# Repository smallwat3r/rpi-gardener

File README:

RPI DHT22 SERVER
----------------

This project contains necessarry files and scripts to read temperature and 
humidity data from a DHT22 sensor, wired to a Raspberry Pi 4. It stores the 
results every 2 seconds in a local Sqlite database, and renders them on a bare 
simple frontend using ChartJS powered by Flask and web-sockets.

REQUIREMENTS
------------

Get and build Python 3.12 from source

    sudo apt update
    sudo apt install build-essential zlib1g-dev libncurses5-dev libgdbm-dev \
        libnss3-dev libssl-dev libreadline-dev libffi-dev libsqlite3-dev
    wget https://python.org/ftp/python/3.12.1/Python-3.12.1.tgz
    tar -xf Python-3.12.1.tgz 
    cd Python-3.12.1
    ./configure --enable-optimizations
    sudo make altinstall

Create a Python virtual environment and install the Python dependencies 
(this is a one-off command)

    make venv deps
    
Install screen to run the commands in the background and keep them persistant

    sudo apt install screen

USAGE
-----

Run the dht sensor polling service
    
    make polling

From another terminal window, run the flask server
    
    make server

Run the commands in screen in order to keep them persistant over the SSH
session
   
    screen -d -m make polling
    screen -d -m make server

You can then list the running screen sessions with
   
    screen -ls

More screen commands see

    screen --help

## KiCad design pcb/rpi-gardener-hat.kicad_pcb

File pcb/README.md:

# RPi Gardener HAT

A custom PCB that combines a Raspberry Pi HAT with an integrated Raspberry Pi Pico for the RPi Gardener project.

## Contents

| Section | Description |
|---------|-------------|
| [PCB](#pcb) | Board specifications, components, pinouts, manufacturing |
| [Case](#case) | 3D printable base and display plates |
| [Assembly](#assembly) | Hardware requirements, stack diagram, build steps |
| [Troubleshooting](#troubleshooting) | Common issues and solutions |

---

## PCB Hat

### Overview

This PCB serves as a unified interface board that:
- Mounts directly on a Raspberry Pi as a HAT (Hardware Attached on Top)
- Integrates a Raspberry Pi Pico for analog sensor readings
- Provides connectors for all sensors and displays

### Board Specifications

| Property | Value |
|----------|-------|
| Dimensions | 65mm x 56mm (standard RPi HAT size) |
| Layers | 2 (F.Cu, B.Cu) |
| Thickness | 1.6mm |
| Mounting Holes | 4x M3 at standard HAT positions |
| Ground Planes | Both layers (unified GND net) |
| KiCad Version | 9.x |

### Components

#### Connectors

| Ref | Description | Pins | Connection |
|-----|-------------|------|------------|
| J1 | RPi GPIO Header | 2x20 | Raspberry Pi 40-pin GPIO |
| J2 | OLED Display (RPi) | 1x4 | I2C SSD1306 128x64 |
| J3 | LCD Display | 1x4 | I2C 1602A with PCF8574 |
| J4 | DHT22 Sensor | 1x3 | Temperature/Humidity |
| J5 | OLED Display (Pico) | 1x4 | I2C SSD1306 128x64 |
| J6 | Moisture Sensor 1 | 1x3 | Capacitive soil sensor |
| J7 | Moisture Sensor 2 | 1x3 | Capacitive soil sensor |
| J8 | Moisture Sensor 3 | 1x3 | Capacitive soil sensor |

#### Modules

| Ref | Description | Footprint |
|-----|-------------|-----------|
| U1 | Raspberry Pi Pico | Through-hole (40 pins) |

#### Mounting

| Ref | Description |
|-----|-------------|
| H1-H4 | M3 mounting holes at standard HAT positions |

### Pin Assignments

#### Raspberry Pi GPIO (directly from J1)

| Function | GPIO | Pin |
|----------|------|-----|
| I2C SDA | GPIO2 | 3 |
| I2C SCL | GPIO3 | 5 |
| DHT22 Data | GPIO17 | 11 |
| 3.3V Power | - | 1, 17 |
| 5V Power | - | 2, 4 |
| Ground | - | 6, 9, 14, 20, 25, 30, 34, 39 |

#### Raspberry Pi Pico (U1)

| Function | GPIO | Pin |
|----------|------|-----|
| OLED SDA | GP0 | 1 |
| OLED SCL | GP1 | 2 |
| Moisture 1 | GP26/ADC0 | 31 |
| Moisture 2 | GP27/ADC1 | 32 |
| Moisture 3 | GP28/ADC2 | 34 |
| 3.3V Out | 3V3 | 36 |
| Ground | GND | 3, 8, 13, 18, 23, 28, 33, 38 |

### Connector Pinouts

#### J2 - OLED RPi (SSD1306 I2C)
```
Pin 1: VCC (3.3V)
Pin 2: GND
Pin 3: SDA (GPIO2)
Pin 4: SCL (GPIO3)
```

#### J3 - LCD I2C (1602A with PCF8574)
```
Pin 1: VCC (5V)
Pin 2: GND
Pin 3: SDA (GPIO2)
Pin 4: SCL (GPIO3)
```

#### J4 - DHT22 Sensor
```
Pin 1: VCC (3.3V)
Pin 2: DATA (GPIO17)
Pin 3: GND
```

#### J5 - OLED Pico (SSD1306 I2C)
```
Pin 1: VCC (Pico 3.3V)
Pin 2: GND
Pin 3: SDA (GP0)
Pin 4: SCL (GP1)
```

#### J6, J7, J8 - Moisture Sensors
```
Pin 1: VCC (Pico 3.3V)
Pin 2: SIG (GP26/GP27/GP28)
Pin 3: GND
```

### I2C Bus Configuration

The board has two separate I2C buses:

#### RPi I2C Bus (GPIO2/GPIO3)
- OLED Display (J2) - typically address 0x3C
- LCD Display (J3) - typically address 0x27 or 0x3F

#### Pico I2C Bus (GP0/GP1)
- OLED Display (J5) - typically address 0x3C

### USB Passthrough

The Pico's USB port is accessible at the board edge for:
- Serial communication with the Raspberry Pi
- Firmware updates
- Debugging

Connect using a USB-A to Micro-USB cable from any RPi USB port to the Pico.

### Files

| File | Description |
|------|-------------|
| `kicad/rpi-gardener-hat.kicad_pro` | KiCad project file |
| `kicad/rpi-gardener-hat.kicad_sch` | Schematic |
| `kicad/rpi-gardener-hat.kicad_pcb` | PCB layout |
| `kicad/rpi-gardener-hat.pretty/` | Custom footprint library |
| `kicad/gerber.zip` | Manufacturing files (Gerber + drill) |

### Manufacturing

Upload `kicad/gerber.zip` to your preferred PCB manufacturer (JLCPCB, PCBWay, etc.).

Recommended settings:
- Layers: 2
- Thickness: 1.6mm
- Surface finish: HASL (lead free) or ENIG
- Copper weight: 1oz
- Solder mask: Any color
- Silkscreen: White

Design rules used:
- Min track width: 0.2mm
- Min clearance: 0.2mm
- Min via diameter: 0.6mm
- Min via drill: 0.3mm

---

## Case

3D printable base and display plates for mounting the full assembly.

### Files

| File | Description |
|------|-------------|
| `case/rpi-gardener-base.scad` | OpenSCAD source for base plate |
| `case/rpi-gardener-base.stl` | Base plate STL |
| `case/rpi-gardener-display-plate.scad` | OpenSCAD source for display plate |
| `case/rpi-gardener-display-plate.stl` | Display plate STL |

### Base Plate

| Property | Value |
|----------|-------|
| Dimensions | 90mm x 62mm x 1.5mm |
| Mounting Pattern | 58mm x 49.5mm (matches RPi/HAT) |
| Hole Diameter | 3.2mm (M3 clearance) |
| Features | Ventilation slots, USB cable cutout |

### Display Plate

| Property | Value |
|----------|-------|
| Dimensions | 90mm x 100mm x 1.5mm |
| OLED Cutouts | 2x 26mm x 15mm (for 0.96" SSD1306) |
| OLED Mount Spacing | 23mm x 23.5mm (M2) |
| LCD Cutout | 73mm x 25mm (for 1602A) |
| LCD Mount Spacing | 75mm x 31mm (M3) |
| Features | Cable routing slots, DHT22 holder tab |

### Printing Settings

- Layer height: 0.2mm
- Infill: 20%
- Material: PLA or PETG
- Supports: Not required

### Regenerating STL

```bash
cd case
openscad -o rpi-gardener-base.stl rpi-gardener-base.scad
openscad -o rpi-gardener-display-plate.stl rpi-gardener-display-plate.scad
```

### Customization

Edit the `.scad` files to adjust dimensions, enable/disable features, or change OLED type (0.96" vs 1.3").

---

## Assembly

### Required Hardware

#### Stack Hardware

| Item | Quantity | Notes |
|------|----------|-------|
| M3 screws | 4 | Bottom, thread into F-M spacers |
| M3 screws | 4 | Top, thread into F-F spacers |
| M3 spacers (5-6mm, F-M) | 4 | Between base and RPi |
| M3 washers (1mm) | 4 | Between RPi and next spacer |
| M3 spacers (10mm, F-M) | 4 | Between RPi and HAT |
| M3 spacers (20mm, F-M) | 4 | Above HAT |
| M3 spacers (5-6mm, F-F) | 4 | Top, screws thread into these |
| Rubber bumpons (8-10mm) | 4 | Anti-slip feet under base plate |

#### Display Mounting

| Item | Quantity | Notes |
|------|----------|-------|
| M2 screws (1mm) | 8 | To attach OLEDs to display plate |
| M2 nuts | 8 | To secure OLEDs |
| M3 screws | 4 | To attach LCD to display plate |
| M3 spacers (5-6mm, F-M) | 4 | Between display plate and LCD |
| M3 nuts | 4 | To secure LCD |
| M3 screw | 1 | Front, to mount DHT22 to display plate pole |
| M3 spacer (F-M) | 1 | Between DHT22 and display plate pole |
| M3 nut | 1 | Back, to secure DHT22 |

#### PCB Components

| Item | Quantity | Notes |
|------|----------|-------|
| 2x16 pin male-to-female header | 2 | For J1 (RPi GPIO), allows RPi plug/unplug |
| 1x4 pin male-to-female header | 3 | For J2, J5 (OLEDs) and J3 (LCD) |
| 1x3 pin male-to-female header | 1 | For J4 (DHT22) |
| Pin headers for Pico | 2x20 | Or solder Pico directly |
| Capacitive soil sensors | 3 | Solder directly to J6, J7, J8 |
| Small dupont wires (M-F) | - | Modules have male pins, HAT has female headers |

**Note:** The RPi 4 has native M2.5 mounting holes. You may need to lightly drill or ream them to fit M3 screws.

### Stack Diagram

```
    ┌─────────────────────┐
    │   4x M3 screws      │  ← Thread into F-F spacers
    ├─────────────────────┤
    │   Display plate     │  ← Top plate with OLEDs + LCD
    ├─────────────────────┤
    │   4x spacers 5-6mm  │  ← F-F (top screws thread here)
    │ + 4x spacers 20mm   │  ← F-M
    ├─────────────────────┤
    │   HAT (PCB)         │  ← RPi Gardener HAT with Pico
    ├─────────────────────┤
    │   4x spacers 10mm   │  ← F-M
    ├─────────────────────┤
    │   4x washers 1mm    │  ← Fine adjustment
    ├─────────────────────┤
    │   Raspberry Pi      │  ← RPi 4
    ├─────────────────────┤
    │   4x spacers 5-6mm  │  ← F-M
    ├─────────────────────┤
    │   Base plate        │  ← 3D printed base
    ├─────────────────────┤
    │   4x M3 screws      │  ← Thread into F-M spacers
    └─────────────────────┘
```

### Assembly Steps

1. **Solder Components to HAT**
   - Solder 2x 16-pin male-to-female headers for J1 (RPi GPIO)
   - Solder 1x4 pin male-to-female headers for J2, J5 (OLEDs) and J3 (LCD)
   - Solder 1x3 pin male-to-female header for J4 (DHT22)
   - Solder capacitive soil sensors directly to J6, J7, J8
   - Mount Pico: solder directly or use pin headers

2. **Mount Displays to Plate**
   - Attach OLEDs using 8x M2 screws (1mm) and 8x M2 nuts
   - Attach LCD using 4x M3 screws, 4x M3 spacers (5-6mm F-M), and 4x M3 nuts

3. **Build the Stack**
   - Insert 4x M3 screws from bottom through base plate into 4x 5-6mm F-M spacers
   - Place Raspberry Pi onto spacers
   - Add 4x 1mm washers
   - Add 4x 10mm F-M spacers
   - Mount HAT, seating GPIO connector onto RPi header
   - Add 4x 20mm F-M spacers
   - Add 4x 5-6mm F-F spacers

4. **Connect Peripherals**
   - Connect OLED displays to J2, J5 using dupont wires
   - Connect LCD 1602A to J3 using dupont wires
   - Connect DHT22 to J4 using dupont wires
   - Connect Pico USB to RPi USB port

5. **Secure Top Plate**
   - Place display plate on top
   - Secure with 4x M3 screws from top

6. **Mount DHT22 Sensor**
   - Attach DHT22 to display plate pole using M3 screw (front), M3 spacer F-M, and M3 nut (back)

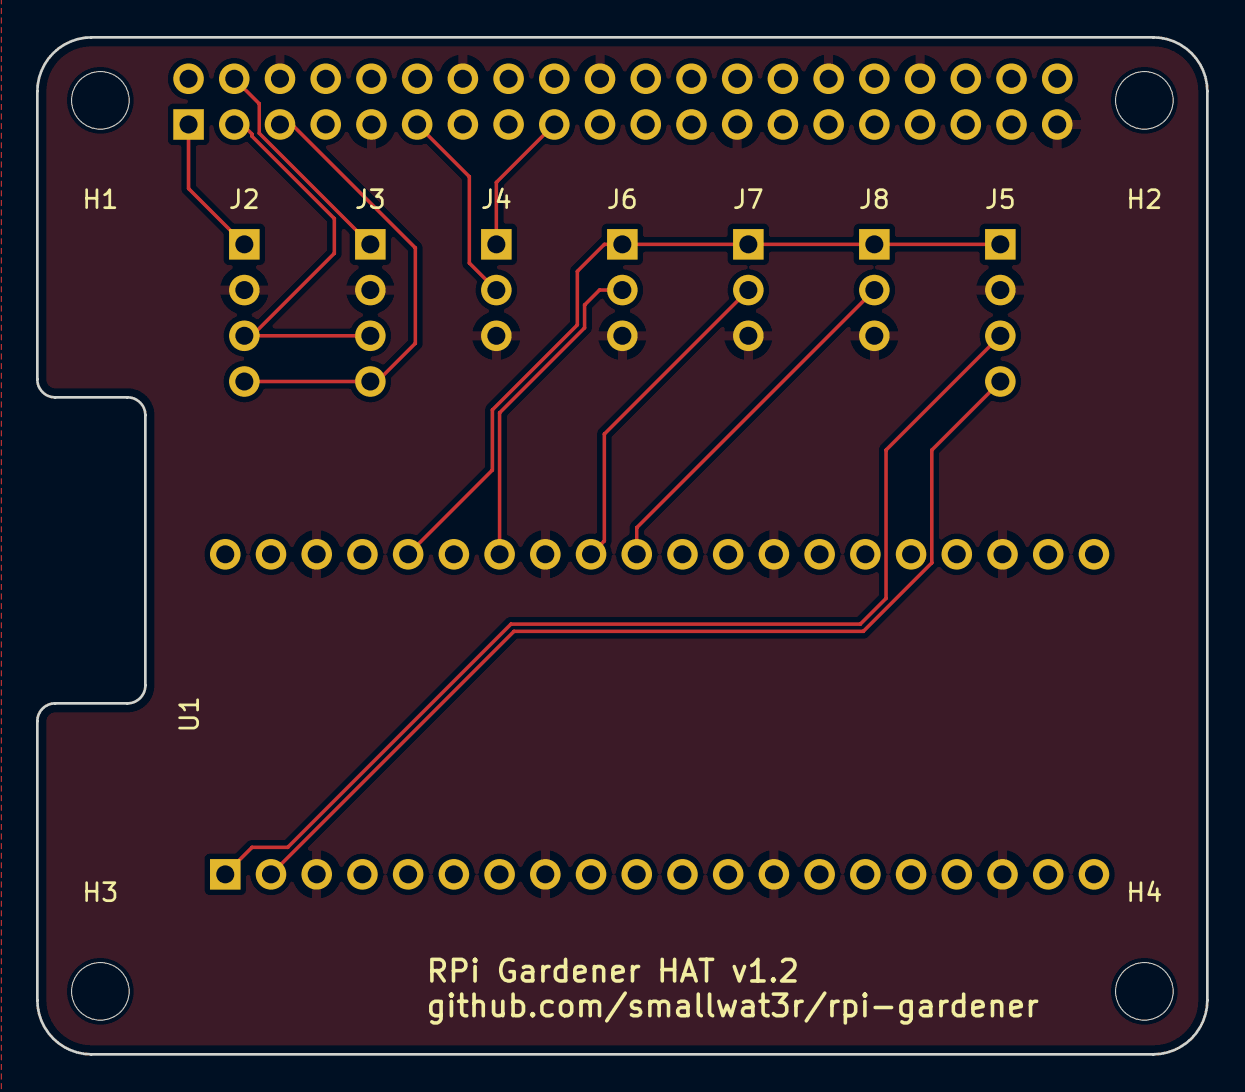
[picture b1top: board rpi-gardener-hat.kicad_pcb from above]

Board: 2 copper layers, 65.0 x 56.5 mm, 13 parts (1 on the bottom side), 12 nets.

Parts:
H1, H2, H3, H4: MH; MountingHole_3.2mm_M3
J1: RPi_GPIO; PinSocket_2x20_P2.54mm_Vertical
J2: OLED_RPi; PinHeader_1x04_P2.54mm_Vertical
J3: LCD_I2C; PinHeader_1x04_P2.54mm_Vertical
J4: DHT22; PinHeader_1x03_P2.54mm_Vertical
J5: OLED_Pico; PinHeader_1x04_P2.54mm_Vertical
J6: MOIST1; PinHeader_1x03_P2.54mm_Vertical
J7: MOIST2; PinHeader_1x03_P2.54mm_Vertical
J8: MOIST3; PinHeader_1x03_P2.54mm_Vertical
U1: Pico; RPi_Pico_SMD_TH

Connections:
+3V3: J1.1 (3V3), J1.17 (3V3), J2.1 (VCC), J4.1 (VCC)
+5V: J1.2 (5V), J1.4 (5V), J3.1 (VCC)
GND: J1.6 (GND), J1.9 (GND), J1.14 (GND), J1.20 (GND), J1.25 (GND), J1.30 (GND), J1.34 (GND), J1.39 (GND), J2.2 (GND), J3.2 (GND), J4.3 (GND), J5.2 (GND), J6.3 (GND), J7.3 (GND), J8.3 (GND), U1.3 (GND), U1.8 (GND), U1.13 (GND), U1.18 (GND), U1.23 (GND), U1.28 (GND), U1.33 (AGND), U1.38 (GND)
GP0_SDA: J5.3 (SDA), U1.1 (GP0)
GP1_SCL: J5.4 (SCL), U1.2 (GP1)
GP26_ADC0: J8.2 (SIG), U1.31 (GP26/ADC0)
GP27_ADC1: J7.2 (SIG), U1.32 (GP27/ADC1)
GP28_ADC2: J6.2 (SIG), U1.34 (GP28/ADC2)
GPIO17_DHT: J1.11 (GPIO17), J4.2 (DATA)
I2C_SCL: J1.5 (GPIO3/SCL1), J2.4 (SCL), J3.4 (SCL)
I2C_SDA: J1.3 (GPIO2/SDA1), J2.3 (SDA), J3.3 (SDA)
PICO_3V3: J5.1 (VCC), J6.1 (VCC), J7.1 (VCC), J8.1 (VCC), U1.36 (3V3_OUT)

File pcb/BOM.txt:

Bill of Materials - RPi Gardener HAT v1.2 (Compact)
==========================================

Connectors
----------
| Ref | Description                    | Qty | Footprint                           |
|-----|--------------------------------|-----|-------------------------------------|
| J1  | 2x20 Pin Socket Header         | 1   | PinSocket_2x20_P2.54mm_Vertical     |
| J2  | 1x4 Pin Header (OLED RPi)      | 1   | PinHeader_1x04_P2.54mm_Vertical     |
| J3  | 1x4 Pin Header (LCD I2C)       | 1   | PinHeader_1x04_P2.54mm_Vertical     |
| J4  | 1x3 Pin Header (DHT22)         | 1   | PinHeader_1x03_P2.54mm_Vertical     |
| J5  | 1x4 Pin Header (OLED Pico)     | 1   | PinHeader_1x04_P2.54mm_Vertical     |
| J6  | 1x3 Pin Header (Moisture 1)    | 1   | PinHeader_1x03_P2.54mm_Vertical     |
| J7  | 1x3 Pin Header (Moisture 2)    | 1   | PinHeader_1x03_P2.54mm_Vertical     |
| J8  | 1x3 Pin Header (Moisture 3)    | 1   | PinHeader_1x03_P2.54mm_Vertical     |

Modules
-------
| Ref | Description                    | Qty | Footprint                           |
|-----|--------------------------------|-----|-------------------------------------|
| U1  | Raspberry Pi Pico              | 1   | RPi_Pico_SMD_TH                     |

Mechanical
----------
| Ref | Description                    | Qty | Footprint                           |
|-----|--------------------------------|-----|-------------------------------------|
| H1-H4| M3 Mounting Holes             | 4   | MountingHole_3.2mm_M3               |

Additional Hardware (for assembly with 3D printed base)
-------------------------------------------------------
| Item                  | Qty | Notes                              |
|-----------------------|-----|------------------------------------|
| M3 x 25-30mm screws   | 4   | Length depends on spacer height    |
| M3 nuts               | 4   | To secure on top of HAT            |
| M3 spacers (5-6mm)    | 4   | Between base and RPi               |
| M3 spacers (10-12mm)  | 4   | Between RPi and HAT                |


PIN ASSIGNMENTS
===============

RPi GPIO Header (J1)
--------------------
Pin 1  (3V3)     -> Power rail for 3.3V sensors
Pin 2  (5V)      -> Power for LCD
Pin 3  (GPIO2)   -> I2C SDA (OLED, LCD)
Pin 4  (5V)      -> Power
Pin 5  (GPIO3)   -> I2C SCL (OLED, LCD)
Pin 6  (GND)     -> Ground
Pin 11 (GPIO17)  -> DHT22 Data
Pin 9,14,20,25,30,34,39 -> GND

OLED RPi (J2) - SSD1306 128x64
------------------------------
Pin 1: VCC (3.3V)
Pin 2: GND
Pin 3: SDA (GPIO2)
Pin 4: SCL (GPIO3)

LCD I2C (J3) - 1602A with PCF8574
---------------------------------
Pin 1: VCC (5V)
Pin 2: GND
Pin 3: SDA (GPIO2)
Pin 4: SCL (GPIO3)

DHT22 (J4)
----------
Pin 1: VCC (3.3V)
Pin 2: DATA (GPIO17)
Pin 3: GND

Pico (U1)
---------
Pin 1  (GP0)  -> OLED SDA
Pin 2  (GP1)  -> OLED SCL
Pin 31 (GP26) -> Moisture Sensor 1
Pin 32 (GP27) -> Moisture Sensor 2
Pin 34 (GP28) -> Moisture Sensor 3
Pin 36 (3V3)  -> Power for Pico peripherals

OLED Pico (J5) - SSD1306 128x64
-------------------------------
Pin 1: VCC (Pico 3.3V)
Pin 2: GND
Pin 3: SDA (GP0)
Pin 4: SCL (GP1)

Moisture Sensors (J6, J7, J8)
-----------------------------
Pin 1: VCC (Pico 3.3V)
Pin 2: Signal (GP26/GP27/GP28)
Pin 3: GND


I2C BUS NOTES
=============
Both OLED (RPi) and LCD share the same I2C bus on GPIO2/GPIO3.
- OLED modules typically use address 0x3C
- LCD backpacks use 0x27 or 0x3F
Check for address conflicts if devices don't respond.


PCB DIMENSIONS
==============
- Total board size: 65mm x 56mm (standard RPi HAT size)
- Compact design with Pico integrated on same footprint
- Pico USB port extends slightly past right edge for access
- Mounting holes: M3 at standard HAT positions (3.5mm from edges)
- 2-layer board, 1.6mm thickness recommended


ASSEMBLY NOTES
==============
1. Solder the 40-pin header (J1) first - ensure alignment with RPi
2. Solder pin headers for connectors (J2-J8)
3. Solder the Pico module last (or use pin headers for removability)
4. Optional: Use female headers for Pico to allow removal


USB PASSTHROUGH
===============
The Pico's USB port is accessible for direct connection to the RPi.
Use a USB-A to Micro-USB cable from any RPi USB port to the Pico.
This provides:
- Serial communication for moisture sensor data
- Programming/firmware updates for the Pico

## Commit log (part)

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2025-12-23 Use preact and clean things up
2025-12-23 Fix requirements
2025-12-23 Clean up
2025-12-23 Fixes
2025-12-23 Refactor
2025-12-23 Add Sqlite adapter for datetime
2025-12-23 Clean config
2025-12-23 Switch to deterministic cleanup
2025-12-23 Add moisture alerts
2025-12-23 Optimise DB queries
2025-12-23 Fix fonts
2025-12-24 Better charts
2025-12-24 Use env_file
2025-12-24 Add wiring tables
2025-12-24 Use serial
2025-12-24 Use asyncio
2025-12-24 Rename module
2025-12-24 Serve SPA from NGINX
2025-12-24 Remove unnecessary endpoint
2025-12-24 Add tests
2025-12-24 Add Slack
2025-12-24 Remove unused
2025-12-24 Add missing deps
2025-12-24 Fix certgen
2025-12-24 Improvements
2025-12-24 Fix tests
2025-12-24 Use plant-ID enum
2025-12-24 Better support for DB ids
2025-12-24 Add validation to dev entrypoint
2025-12-24 Better docker setup
2025-12-24 Use uv for deps management
2025-12-24 Use async DB
2025-12-24 Fix entrypoint
2025-12-24 Upgrade vite
2025-12-24 Better usage of config
2025-12-24 Add transaction support
2025-12-24 Configure logging as early as possible
2025-12-24 Ensure this is closed cleanly
2025-12-24 Use timeouts
2025-12-24 Better way to use config
2025-12-24 Type type alias
2025-12-24 Remove dead code
2025-12-24 Patch sleep calls in tests
2025-12-25 Migrate to Python 3.14
2025-12-25 Better docker configs
2025-12-25 Add modals to see graphs
2025-12-25 Update image
2025-12-25 Ability to mock sensors for development
2025-12-25 Use entrypoint files
2025-12-25 Use app factory pattern
2025-12-25 Isort
2025-12-25 Refactors
2025-12-25 Better typing
2025-12-25 Better way to generate mock data
2025-12-25 Use crontab to do database clean up
2025-12-25 Add event bus architecture
2025-12-25 Remove flag
2025-12-25 Use Redis based broker
2025-12-26 Simplify stats calculation
2025-12-26 Format and lint
2025-12-26 Enforce MYPY
2025-12-26 Clean ups
2025-12-26 Add settings modal
2025-12-26 Refactor validators
2025-12-26 Use Pydantic
2025-12-26 Lint and fmt
2025-12-26 Larger modals
2025-12-26 Better modals
2025-12-26 Better use of Pydantic validation
2025-12-26 Improve CI
2025-12-26 Fix pre-commit
2025-12-26 Better pattern to count for deleted records
2025-12-26 Better UI to select timeframes
2025-12-26 Use buckets for faster queries
2025-12-26 Update dashboard image
2025-12-26 Add hysteresis for alert notifications
2025-12-26 Use context manager
2025-12-26 Improve health checks
2025-12-27 Make classes private
2025-12-27 Fix N+1 queries
2025-12-27 Use executemany
2025-12-27 Move test utils to conftest
2025-12-27 Use DI pattern
2025-12-27 Add comment about setting_override var
2025-12-27 Refactor alert state checks
2025-12-27 Make most classes in config internal
2025-12-27 Rename targets
2025-12-27 Remove unused code
2026-01-02 Remove unused configs
2026-01-02 Edit READMEs
2026-01-02 Add pico sync script
2026-01-02 Auto detect Pico port
2026-01-02 Fix modals for mobile
2026-01-02 Better subjects
2026-01-02 Better mobile
2026-01-02 Mobile fix
2026-01-02 Use requests
2026-01-02 More scrollable area
2026-01-02 Mobile fixes
2026-01-02 Better displays
2026-01-02 Better DHT display
2026-01-02 Add .local hostname
2026-01-03 Simplify alert emails
2026-01-04 All loading indicators for graphs
2026-01-05 Fix CSP
2026-01-05 Better logic
2026-01-05 Simplify logging
2026-01-05 Better implementation
2026-01-05 Better email alerts
2026-01-05 Add to env example
2026-01-05 Remove code duplication
2026-01-06 Ensure it scales if we add more kasa
2026-01-06 Better spinner
2026-01-06 Better management of spikes in moisture
2026-01-06 Rename var for consistency
2026-01-06 Add 1602A LCD for alerts
2026-01-06 Add info
2026-01-06 Fix validator
2026-01-06 Increase
2026-01-06 Add OLED service similar to LCD
2026-01-06 Refactor services
2026-01-06 Add retries for smartplug
2026-01-06 Use enum for configs
2026-01-06 Fix depreciation warning
2026-01-06 Add humidifier icon on FE
2026-01-06 Add icon for when humidifier is on
2026-01-06 Move db cleanup to cron
2026-01-07 Add gerber file
2026-01-08 Mounts for displays
2026-01-08 Better query management
2026-01-08 Use INTEGER and not TEXT for timestamps
2026-01-08 Better management of queries
2026-01-08 Better query
2026-01-08 Even better
2026-01-08 Optimisations
2026-01-08 Fix query
2026-01-08 Holder for DHT
2026-01-09 Update BOM
2026-01-10 Add note about M2.5
2026-01-12 Update STL
2026-01-12 PCB (#13)
    * PCB
    * WIP
    * Updated
    * Fix
    * Add gerber file
    * Fix
2026-01-13 Update READMEs
2026-01-13 Add missing assembly step for DHT22
2026-01-22 Fix connection pool
2026-01-22 Fix global state for cache settings
2026-01-22 Ensure code is async-safe
2026-01-22 Fix comment
2026-01-22 Better settings cache
2026-01-25 Fix bugs
2026-01-25 Remove unused state
2026-01-25 Remove dead code from tests too
2026-01-25 Clean up alert tracker
2026-01-25 Fix code duplication
2026-01-25 Split config
2026-01-25 Fix imports
2026-01-26 Remove deprecated path
2026-01-26 Remove blank lines
2026-01-26 Use shared method
2026-01-26 Use plant ID constants
2026-01-26 Use SSE instead of websockets
2026-01-26 Fix for mock sensors
2026-01-26 Fix mock sensors
2026-01-26 Remove logs
2026-03-07 Update directory name
2026-03-27 Bump deps
2026-04-16 Bump aiohttp from 3.13.3 to 3.13.4
    ---
    updated-dependencies:
    - dependency-name: aiohttp
    dependency-version: 3.13.4
    dependency-type: indirect
    ...
2026-05-12 Bump urllib3 from 2.6.3 to 2.7.0
    Bumps [urllib3](https://github.com/urllib3/urllib3) from 2.6.3 to 2.7.0.
    - [Release notes](https://github.com/urllib3/urllib3/releases)
    - [Changelog](https://github.com/urllib3/urllib3/blob/main/CHANGES.rst)
    - [Commits](https://github.com/urllib3/urllib3/compare/2.6.3...2.7.0)
    ---
    updated-dependencies:
2026-05-12 Bump urllib3 from 2.6.3 to 2.7.0 (#16)
    Bumps [urllib3](https://github.com/urllib3/urllib3) from 2.6.3 to 2.7.0.
    - [Release notes](https://github.com/urllib3/urllib3/releases)
    - [Changelog](https://github.com/urllib3/urllib3/blob/main/CHANGES.rst)
    - [Commits](https://github.com/urllib3/urllib3/compare/2.6.3...2.7.0)
    ---
    updated-dependencies:
2026-05-27 Bump vite from 6.4.1 to 6.4.2 in /rpi/server/frontend
    Bumps [vite](https://github.com/vitejs/vite/tree/HEAD/packages/vite) from 6.4.1 to 6.4.2.
    - [Release notes](https://github.com/vitejs/vite/releases)
    - [Changelog](https://github.com/vitejs/vite/blob/v6.4.2/packages/vite/CHANGELOG.md)
    - [Commits](https://github.com/vitejs/vite/commits/v6.4.2/packages/vite)
    ---
    updated-dependencies:
2026-05-27 Bump python-dotenv from 1.2.1 to 1.2.2
    Bumps [python-dotenv](https://github.com/theskumar/python-dotenv) from 1.2.1 to 1.2.2.
    - [Release notes](https://github.com/theskumar/python-dotenv/releases)
    - [Changelog](https://github.com/theskumar/python-dotenv/blob/main/CHANGELOG.md)
    - [Commits](https://github.com/theskumar/python-dotenv/compare/v1.2.1...v1.2.2)
    ---
    updated-dependencies:
2026-05-28 Bump vite from 6.4.1 to 6.4.2 in /rpi/server/frontend (#17)
    Bumps [vite](https://github.com/vitejs/vite/tree/HEAD/packages/vite) from 6.4.1 to 6.4.2.
    - [Release notes](https://github.com/vitejs/vite/releases)
    - [Changelog](https://github.com/vitejs/vite/blob/v6.4.2/packages/vite/CHANGELOG.md)
    - [Commits](https://github.com/vitejs/vite/commits/v6.4.2/packages/vite)
    ---
    updated-dependencies:
2026-05-28 Bump python-dotenv from 1.2.1 to 1.2.2 (#18)
    Bumps [python-dotenv](https://github.com/theskumar/python-dotenv) from 1.2.1 to 1.2.2.
    - [Release notes](https://github.com/theskumar/python-dotenv/releases)
    - [Changelog](https://github.com/theskumar/python-dotenv/blob/main/CHANGELOG.md)
    - [Commits](https://github.com/theskumar/python-dotenv/compare/v1.2.1...v1.2.2)
    ---
    updated-dependencies:
2026-05-28 Bump pillow from 12.1.1 to 12.2.0 (#19)
    Bumps [pillow](https://github.com/python-pillow/Pillow) from 12.1.1 to 12.2.0.
    - [Release notes](https://github.com/python-pillow/Pillow/releases)
    - [Changelog](https://github.com/python-pillow/Pillow/blob/main/CHANGES.rst)
    - [Commits](https://github.com/python-pillow/Pillow/compare/12.1.1...12.2.0)
    ---
    updated-dependencies:
2026-05-28 Bump cryptography from 46.0.6 to 46.0.7
    Bumps [cryptography](https://github.com/pyca/cryptography) from 46.0.6 to 46.0.7.
    - [Changelog](https://github.com/pyca/cryptography/blob/main/CHANGELOG.rst)
    - [Commits](https://github.com/pyca/cryptography/compare/46.0.6...46.0.7)
    ---
    updated-dependencies:
    - dependency-name: cryptography
2026-05-28 Bump postcss from 8.5.6 to 8.5.15 in /rpi/server/frontend
    Bumps [postcss](https://github.com/postcss/postcss) from 8.5.6 to 8.5.15.
    - [Release notes](https://github.com/postcss/postcss/releases)
    - [Changelog](https://github.com/postcss/postcss/blob/main/CHANGELOG.md)
    - [Commits](https://github.com/postcss/postcss/compare/8.5.6...8.5.15)
    ---
    updated-dependencies:
2026-05-28 Bump pygments from 2.19.2 to 2.20.0
    Bumps [pygments](https://github.com/pygments/pygments) from 2.19.2 to 2.20.0.
    - [Release notes](https://github.com/pygments/pygments/releases)
    - [Changelog](https://github.com/pygments/pygments/blob/master/CHANGES)
    - [Commits](https://github.com/pygments/pygments/compare/2.19.2...2.20.0)
    ---
    updated-dependencies:
2026-05-28 Bump pytest from 9.0.2 to 9.0.3
    Bumps [pytest](https://github.com/pytest-dev/pytest) from 9.0.2 to 9.0.3.
    - [Release notes](https://github.com/pytest-dev/pytest/releases)
    - [Changelog](https://github.com/pytest-dev/pytest/blob/main/CHANGELOG.rst)
    - [Commits](https://github.com/pytest-dev/pytest/compare/9.0.2...9.0.3)
    ---
    updated-dependencies:
2026-05-28 Bump pytest from 9.0.2 to 9.0.3 (#24)
    Bumps [pytest](https://github.com/pytest-dev/pytest) from 9.0.2 to 9.0.3.
    - [Release notes](https://github.com/pytest-dev/pytest/releases)
    - [Changelog](https://github.com/pytest-dev/pytest/blob/main/CHANGELOG.rst)
    - [Commits](https://github.com/pytest-dev/pytest/compare/9.0.2...9.0.3)
    ---
    updated-dependencies:
2026-05-28 Bump postcss from 8.5.6 to 8.5.15 in /rpi/server/frontend (#22)
    Bumps [postcss](https://github.com/postcss/postcss) from 8.5.6 to 8.5.15.
    - [Release notes](https://github.com/postcss/postcss/releases)
    - [Changelog](https://github.com/postcss/postcss/blob/main/CHANGELOG.md)
    - [Commits](https://github.com/postcss/postcss/compare/8.5.6...8.5.15)
    ---
    updated-dependencies:
2026-05-28 Bump idna from 3.11 to 3.15 (#21)
    Bumps [idna](https://github.com/kjd/idna) from 3.11 to 3.15.
    - [Release notes](https://github.com/kjd/idna/releases)
    - [Changelog](https://github.com/kjd/idna/blob/master/HISTORY.md)
    - [Commits](https://github.com/kjd/idna/compare/v3.11...v3.15)
    ---
    updated-dependencies:
2026-05-28 Bump cryptography from 46.0.6 to 46.0.7 (#20)
    Bumps [cryptography](https://github.com/pyca/cryptography) from 46.0.6 to 46.0.7.
    - [Changelog](https://github.com/pyca/cryptography/blob/main/CHANGELOG.rst)
    - [Commits](https://github.com/pyca/cryptography/compare/46.0.6...46.0.7)
    ---
    updated-dependencies:
    - dependency-name: cryptography
2026-06-17 Bump esbuild, @preact/preset-vite and vite in /rpi/server/frontend
    Removes [esbuild](https://github.com/evanw/esbuild). It's no longer used after updating ancestor dependencies [esbuild](https://github.com/evanw/esbuild), [@preact/preset-vite](https://github.com/pre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
    Removes `esbuild`
    Updates `@preact/preset-vite` from 2.10.2 to 2.10.5
    - [Release notes](https://github.com/preactjs/preset-vite/releases)
    - [Commits](https://github.com/preactjs/preset-vite/compare/2.10.2...2.10.5)
    Updates `vite` from 6.4.2 to 8.0.16
2026-06-25 Add Tailscale certificates
2026-06-25 Add renewal script
2026-06-25 Fix script
